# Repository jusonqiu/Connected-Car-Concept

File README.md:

# Connected Car Concept

The Connected Car Project, GateBox, allows you to operate your garage door and front lawn lights from the car's dashboard itself. It does this by having a smartphone interact with a gateway panel (the GateBox panel) that is placed within the garage. The smartphone is mirrored onto the car's dashboard. This is possible using a number of Connected Car features which are likely to grow popular in the future such as: Android Auto, Apple CarPlay, MirrorLink, AppLink, etc. This project was entered into the Microsoft Imagine Cup competition of 2015.

Please watch the introduction video below:

<div style="text-align: center">

</div>

The Github.io page is can be seen [here](http://shafeeqr2.github.io/Connected-Car-Concept/ "GateBox").
## Opensource
Since the Microsoft Imagine Cup competition, this project has been released on Github in hopes that it can be improved upon. The orignal app developed is in the "Windows Application Folder". Some of the files that were submitted to Microsoft judges are in the "Imagine Cup Files" folder. These files have been slightly modified since submission. 

## Where to Start?
First read the Bluetooth manuals. They are from the Bluetooth Special Interest Group and aim to teach how to develop Bluetooth Low Energy applications for a number of different platforms  - Android, iOS and Windows Phone.

For the electronics, there are two different ways to approach this project: The Simplified and Detailed way - One method uses a pre-existing Bluetooth LE chip and other method involves making this chip from scratch based on schematics provided. There is a Parts List and the Instructions version for the detailed and the simplified way. It is recommended that you start with the simplified way even if you plan to use the detailed way.

Read through the parts list for the electronics and the case enclosure in the "Parts List" folder. Then, read through the hardware and software instructions in the "Instructions" folder.

##Contribute

If you feel you can improve on a certain aspect of this project or expand upon it, please considering sharing it to be a part of this project.

If you have any questions or concerns, please contact me at: shafeeqr21@gmail.com.

## What are Connected Cars?

### The following expert is from a 2014 CABA (Continental Automated Building Association) report:

*The connected car market, while still in its infancy, has rapidly evolved from a niche capability available in select models to a perceived must-have in the car industry. A connected car, by definition, is one that maintains a wide area connection (typically cellular-based) and often also a local area network (typically Wi-Fi). Via these connections the car is able to send and receive information relevant to the trip/route and the car’s performance/condition.*

*An increasing number of vehicles are coming to market with the capability to support communications of various sorts. In 2013 more than one billion sensors were sold to the auto industry, more than doubling the 2009 levels[1]. While tethered and integrated solutions have dominated car connectivity to date, embedded connectivity solutions began appearing in 2014 with the number of such vehicles increasing in 2015 and beyond.*

*The connected car market is on the cusp of significant growth. A variety of market factors, from government regulations, to industry partnerships, to consumer demand, are propelling the connected car market forward. Consumers got a glimpse of the future of connected cars in 2014 as select models began rolling off the production line with these capabilities, but 2015 promises so much more in terms of number of connected vehicles and the services being delivered to those vehicles.* 

##

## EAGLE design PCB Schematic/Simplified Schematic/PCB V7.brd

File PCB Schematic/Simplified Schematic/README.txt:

The design can be further simplified if you decide to use your own Arduino UNO in which case you need not include the following materials onto PCB (Refer to "PCB V7 board.PNG"):

* DCJACK
* Diode D1
* Capacitors C1, C2, C3, C4
* ATMEGA328P IC1
* Voltage Regulator 7805T IC2
* Quartz Crystal 16MHZ Q1

It would be nice if someone can take the time to make a PCB without these items and in its place leave a line of male headers which would connect to the Arduino UNO as per the following pinouts:

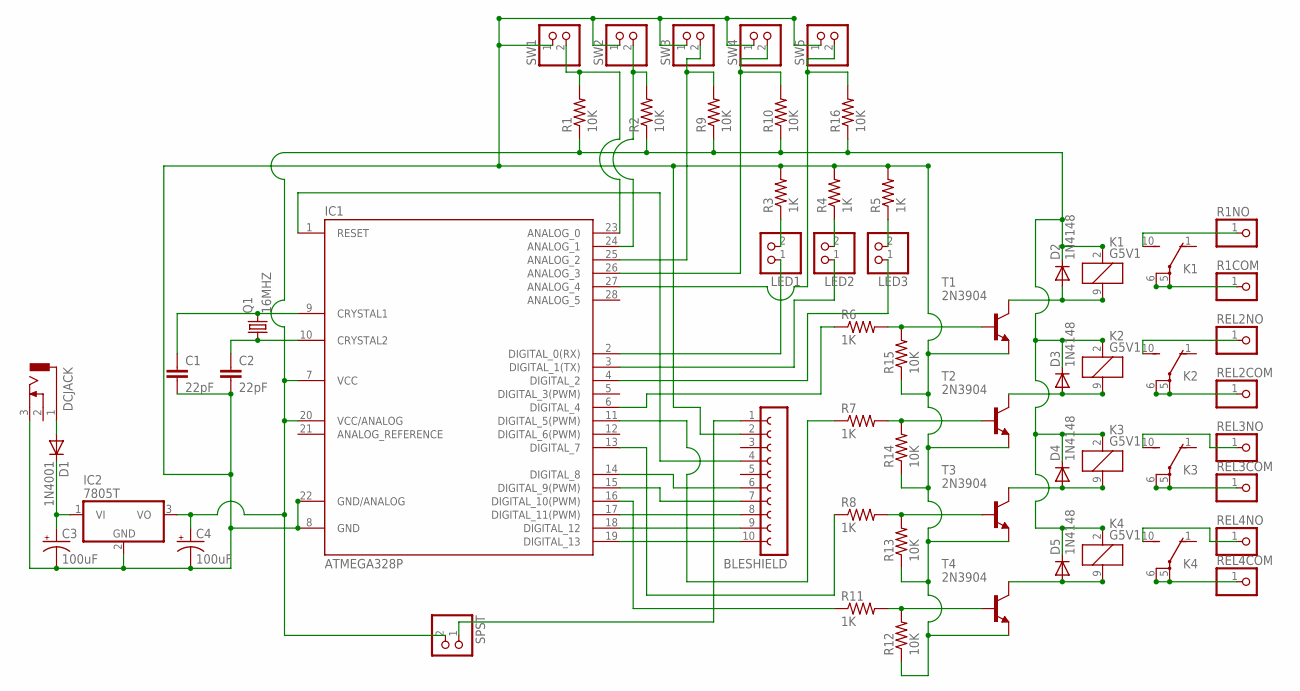
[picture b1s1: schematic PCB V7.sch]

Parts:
BLESHIELD: FE10-1; FE10
C1, C2: 22pF; C025-030X050
C3, C4: 100uF; E2,5-6
D1: 1N4001; DO41-10
D2, D3, D4, D5: 1N4148; DO35-7
DCJACK: DCJ0202
IC1: ATMEGA328P; DIL28-3
IC2: 7805T; TO220H
K1, K2, K3, K4: G5V1
LED1, LED2, LED3: PINHD-1X2; 1X02
Q1: 16MHZ; HC49/S
R1, R2, R9, R10, R12, R13, R14, R15, R16: 10K; 0204/5
R1COM, R1NO: PINHD-1X1; 1X01
R3, R4, R5, R6, R7, R8, R11: 1K; 0204/5
REL2COM, REL2NO, REL3COM, REL3NO, REL4COM, REL4NO: PINHD-1X1; 1X01
SPST: PINHD-1X2; 1X02
SW1, SW2, SW3, SW4, SW5: PINHD-1X2; 1X02
T1, T2, T3, T4: 2N3904; TO92

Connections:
GND: BLESHIELD.2, C1.2, C2.2, C3.-, C4.-, DCJACK.3, IC1.8 (GND), IC1.22 (GND/ANALOG), IC2.2 (GND), R3.2, R4.2, R5.2, R12.1, R13.1, R14.1, R15.1, SW1.1, SW2.1, SW3.1, SW4.1, SW5.1, T1.3 (E), T2.3 (E), T3.3 (E), T4.3 (E)
unnamed: BLESHIELD.10, IC1.19 (DIGITAL_13)
unnamed: R6.2, R15.2, T1.2 (B)
unnamed: IC1.3 (DIGITAL_1(TX)), LED2.1
unnamed: BLESHIELD.6, IC1.14 (DIGITAL_8)
unnamed: C1.1, IC1.9 (CRYSTAL1), Q1.2
unnamed: C2.1, IC1.10 (CRYSTAL2), Q1.1
unnamed: IC1.24 (ANALOG_1), R2.2, SW2.2
unnamed: C3.+, D1.C, IC2.1 (VI)
unnamed: BLESHIELD.4, IC1.1 (RESET)
unnamed: BLESHIELD.7, IC1.15 (DIGITAL_9(PWM))
unnamed: BLESHIELD.8, IC1.17 (DIGITAL_11(PWM))
unnamed: BLESHIELD.9, IC1.18 (DIGITAL_12)
unnamed: D3.A, K2.9 (2), T2.1 (C)
unnamed: R7.2, R14.2, T2.2 (B)
unnamed: IC1.23 (ANALOG_0), R1.2, SW1.2
unnamed: D2.A, K1.9 (2), T1.1 (C)
unnamed: LED1.2, R3.1
unnamed: LED2.2, R4.1
unnamed: LED3.2, R5.1
unnamed: C4.+, D2.C, D3.C, D4.C, D5.C, IC1.7 (VCC), IC1.20 (VCC/ANALOG), IC2.3 (VO), K1.2 (1), K2.2 (1), K3.2 (1), K4.2 (1), R1.1, R2.1, R9.1, R10.1, R16.1, SPST.2
unnamed: IC1.27 (ANALOG_4), R16.2, SW5.2
unnamed: K1.5, K1.6, R1COM.1
unnamed: K1.10 (S), R1NO.1
unnamed: IC1.16 (DIGITAL_10(PWM)), R11.1
unnamed: IC1.25 (ANALOG_2), R9.2, SW3.2
unnamed: IC1.6 (DIGITAL_4), R6.1
unnamed: D1.A, DCJACK.1
unnamed: IC1.26 (ANALOG_3), R10.2, SW4.2
unnamed: IC1.2 (DIGITAL_0(RX)), LED1.1
unnamed: BLESHIELD.1, SPST.1
unnamed: K2.10 (S), REL2NO.1
unnamed: K2.5, K2.6, REL2COM.1
unnamed: K3.5, K3.6, REL3COM.1
unnamed: IC1.13 (DIGITAL_7), R8.1
unnamed: IC1.11 (DIGITAL_5(PWM)), R7.1
unnamed: K3.10 (S), REL3NO.1
unnamed: K4.10 (S), REL4NO.1
unnamed: K4.5, K4.6, REL4COM.1
unnamed: R8.2, R13.2, T3.2 (B)
unnamed: IC1.4 (DIGITAL_2), LED3.1
unnamed: D4.A, K3.9 (2), T3.1 (C)
unnamed: R11.2, R12.2, T4.2 (B)
unnamed: D5.A, K4.9 (2), T4.1 (C)

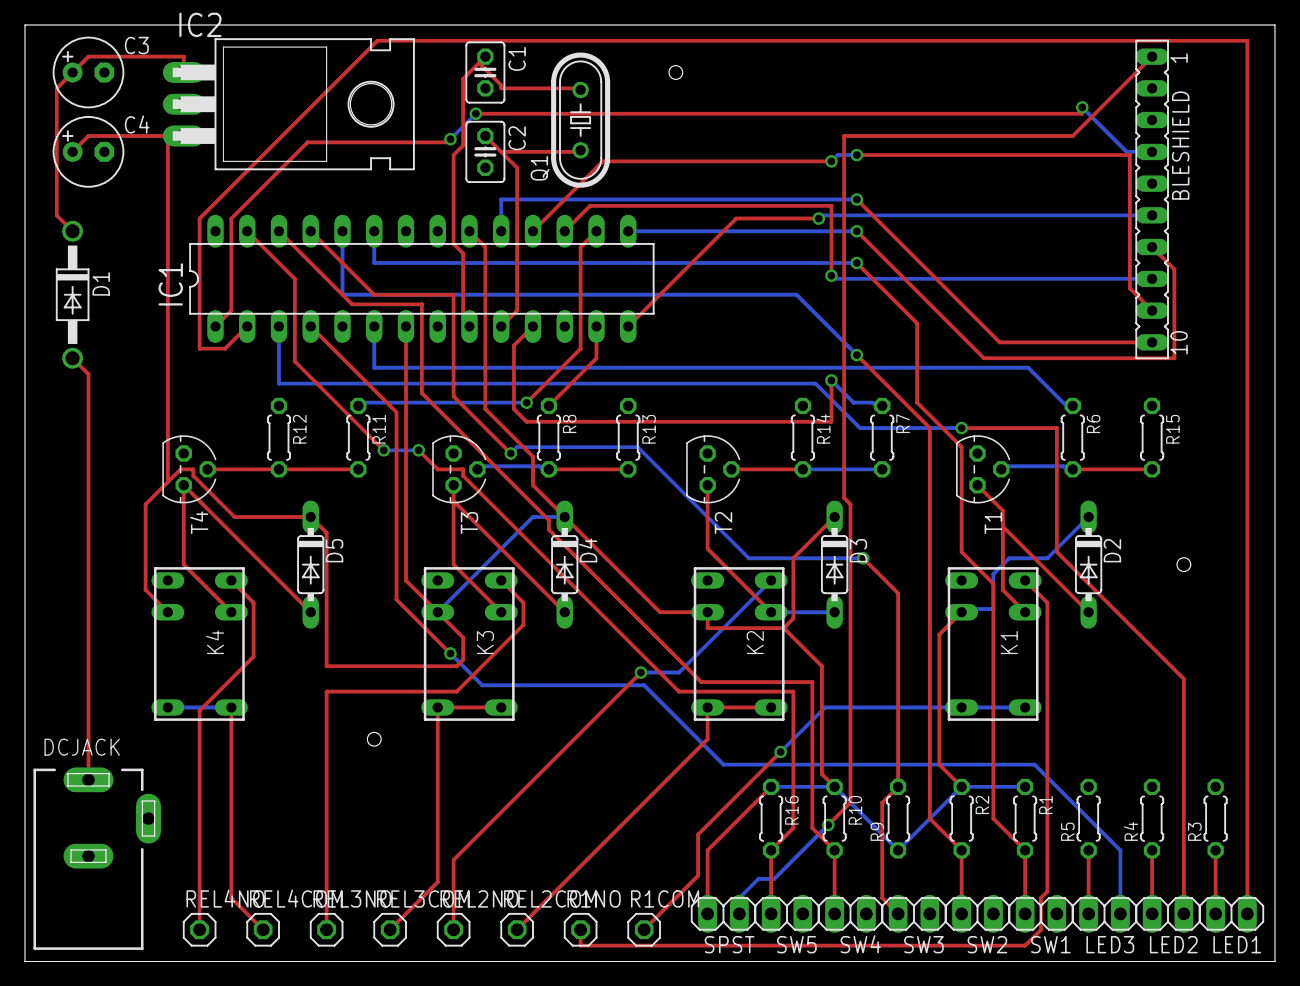
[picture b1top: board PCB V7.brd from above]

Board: 2 copper layers, 100.0 x 74.9 mm, 55 parts (0 on the bottom side), 44 nets.

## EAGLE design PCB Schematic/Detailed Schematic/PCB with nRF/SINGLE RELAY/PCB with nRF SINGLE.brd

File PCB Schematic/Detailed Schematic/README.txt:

The design has been modified since these files have been made.

Would appreciate it if someone could replace the two solid state relays with 4 mechanical relays (as shown in PCB V7 board.PNG in Simplified Schematic folder) and re-route all the wires and push the .brd and .sch files.

Thanks.

Shafeeq.

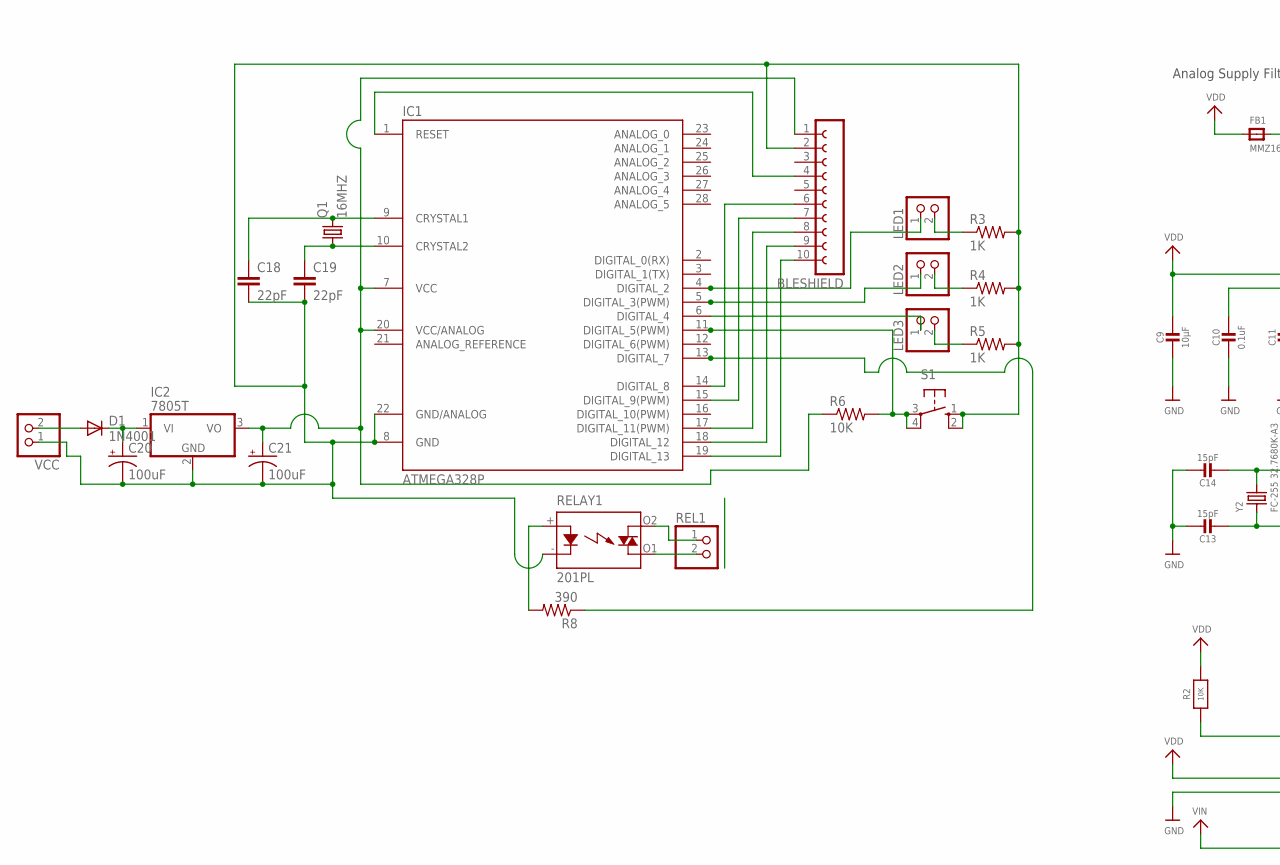
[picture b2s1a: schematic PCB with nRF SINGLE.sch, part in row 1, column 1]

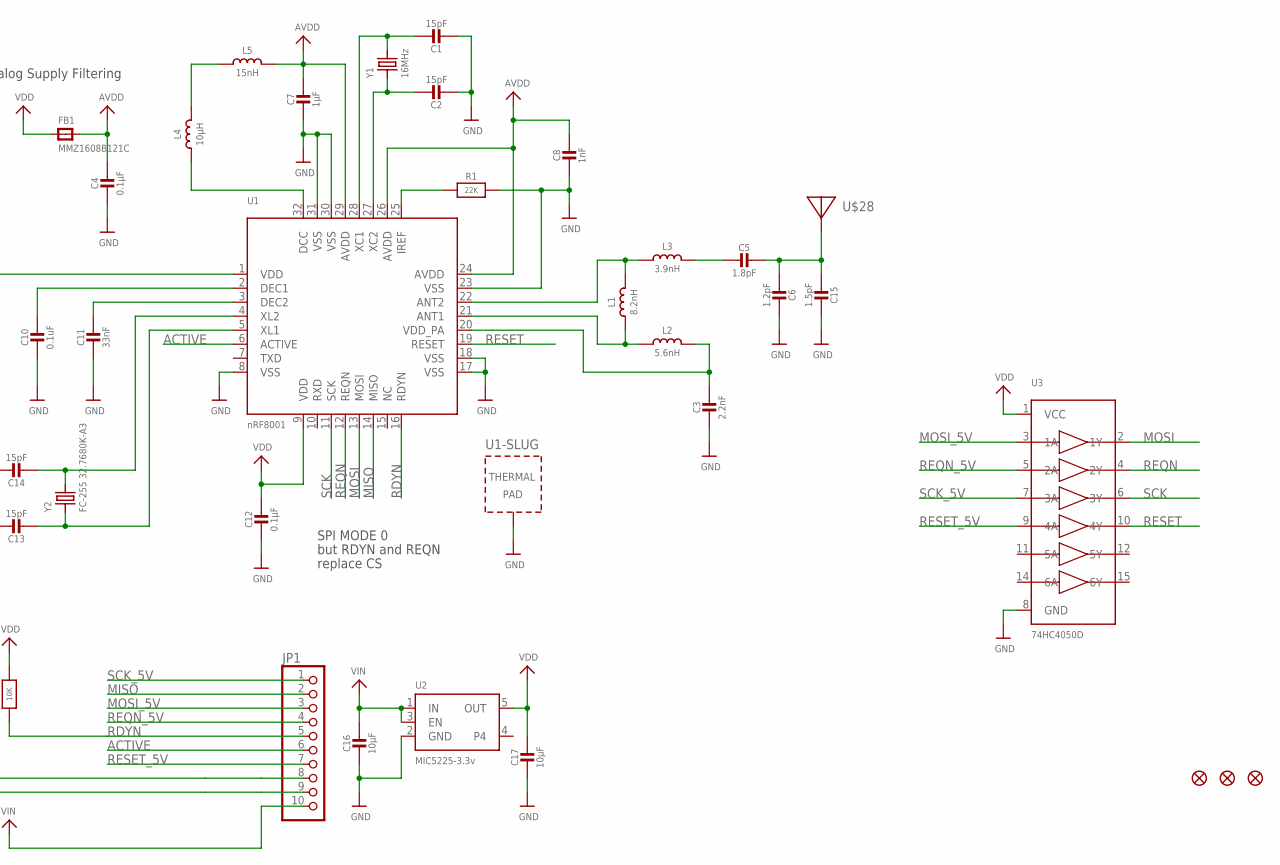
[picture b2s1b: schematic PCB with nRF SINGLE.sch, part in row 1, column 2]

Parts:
BLESHIELD: FE10-1; FE10
C1, C2, C13, C14: 15pF; 0805-NO
C3: 2.2nF; _0402
C4, C12: 0.1µF; 0805-NO
C5: 1.8pF; _0402MP
C6: 1.2pF; _0402MP
C7: 1µF; 0805-NO
C8: 1nF; _0603
C9, C16, C17: 10µF; 0805-NO
C10: 0.1uF; 0805-NO
C11: 33nF; 0805-NO
C15: 1.5pF; _0402MP
C18, C19: 22pF; C025-030X050
C20, C21: 100uF; E2,5-6
D1: 1N4001; DO41-10
FB1: MMZ1608B121C; 0805
FID1, FID2, FID3: FIDUCIAL""; FIDUCIAL_1MM
IC1: ATMEGA328P; DIL28-3
IC2: 7805T; TO220H
JP1: HEADER-1X1070MIL; 1X10_ROUND70
L1: 8.2nH; _0402
L2: 5.6nH; _0402
L3: 3.9nH; _0402
L4: 10µH; _0603
L5: 15nH; _0603
LED1, LED2, LED3: PINHD-1X2; 1X02
Q1: 16MHZ; HC49/S
R1: 22K; _0805MP
R2: 10K; 0805-NO
R3, R4, R5: 1K; 0204/5
R6: 10K; 0204/5
R8: 390; 0204/5
REL1: PINHD-1X2; 1X02
RELAY1: 201PL; AQG
S1: 10-XX; B3F-10XX
U1: nRF8001; QFN32_5MM
U2: MIC5225-3.3v; SOT23-5
U3: 74HC4050D; TSSOP16
U$28: ANTENNA_PCBNRF8001_1.6MM; ANT_PCB_2.4GHZ_NRF8001_1.6MM_1OZ
VCC: PINHD-1X2; 1X02
Y1: 16MHz; CRYSTAL_2.5X2
Y2: FC-255 32.7680K-A3; CRYSTAL_4.9X1.8

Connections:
ACTIVE: JP1.6, U1.6 (ACTIVE)
AVDD: C4.1, C7.1, C8.1, FB1.2, L5.2, U1.24 (AVDD), U1.26 (AVDD), U1.29 (AVDD)
GND: C1.2, C2.2, C3.2, C4.2, C6.1, C7.2, C8.2, C9.2, C10.2, C11.2, C12.2, C13.1, C14.1, C15.1, C16.2, C17.2, JP1.9, R1.2, U1.8 (VSS), U1.17 (VSS), U1.18 (VSS), U1.23 (VSS), U1.30 (VSS), U1.31 (VSS), U1.33 (TP), U2.2 (GND), U3.8 (GND)
MISO: JP1.2, U1.14 (MISO)
MOSI: U1.13 (MOSI), U3.2 (1Y)
MOSI_5V: JP1.3, U3.3 (1A)
unnamed: BLESHIELD.10, IC1.19 (DIGITAL_13)
unnamed: L1.2, L3.1, U1.22 (ANT2)
unnamed: L1.1, L2.1, U1.21 (ANT1)
unnamed: C3.1, L2.2, U1.20 (VDD_PA)
unnamed: L4.2, L5.1
unnamed: C5.2, L3.2
unnamed: C11.1, U1.3 (DEC2)
unnamed: C10.1, U1.2 (DEC1)
unnamed: C1.1, U1.28 (XC1), Y1.3 (2)
unnamed: C2.1, U1.27 (XC2), Y1.1
unnamed: L4.1, U1.32 (DCC)
unnamed: R1.1, U1.25 (IREF)
unnamed: C5.1, C6.2, C15.2, U$28.FEED
unnamed: C18.1, IC1.9 (CRYSTAL1), Q1.2
unnamed: C19.1, IC1.10 (CRYSTAL2), Q1.1
unnamed: BLESHIELD.6, IC1.14 (DIGITAL_8)
unnamed: BLESHIELD.7, IC1.15 (DIGITAL_9(PWM))
unnamed: BLESHIELD.8, IC1.17 (DIGITAL_11(PWM))
unnamed: BLESHIELD.9, IC1.18 (DIGITAL_12)
unnamed: BLESHIELD.1, C21.+, IC1.7 (VCC), IC1.20 (VCC/ANALOG), IC2.3 (VO), R6.1
unnamed: BLESHIELD.4, IC1.1 (RESET)
unnamed: C14.2, U1.4 (XL2), Y2.2
unnamed: C13.2, U1.5 (XL1), Y2.1
unnamed: IC1.4 (DIGITAL_2), LED1.1
unnamed: IC1.5 (DIGITAL_3(PWM)), LED2.1
unnamed: LED1.2, R3.1
unnamed: LED2.2, R4.1
unnamed: LED3.2, R5.1
unnamed: IC1.11 (DIGITAL_5(PWM)), R6.2, S1.3, S1.4 (P1)
unnamed: REL1.2, RELAY1.O1 (DS2)
unnamed: IC1.13 (DIGITAL_7), R8.1
unnamed: C20.+, D1.C, IC2.1 (VI)
unnamed: BLESHIELD.2, C18.2, C19.2, C20.-, C21.-, IC1.8 (GND), IC1.22 (GND/ANALOG), IC2.2 (GND), R3.2, R4.2, R5.2, RELAY1.- (K), S1.1 (S), S1.2 (S1), VCC.1
unnamed: D1.A, VCC.2
unnamed: IC1.6 (DIGITAL_4), LED3.1
unnamed: R8.2, RELAY1.+ (A)
RDYN: JP1.5, R2.1, U1.16 (RDYN)
REL1: REL1.1, RELAY1.O2 (DS1)
REQN: U1.12 (REQN), U3.4 (2Y)
REQN_5V: JP1.4, U3.5 (2A)
RESET: U1.19 (RESET), U3.10 (4Y)
RESET_5V: JP1.7, U3.9 (4A)
SCK: U1.11 (SCK), U3.6 (3Y)
SCK_5V: JP1.1, U3.7 (3A)
VDD: C9.1, C12.1, C17.1, FB1.1, JP1.8, R2.2, U1.1 (VDD), U1.9 (VDD), U2.5 (OUT), U3.1 (VCC)
VIN: C16.1, JP1.10, U2.1 (IN), U2.3 (EN)

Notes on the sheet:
Analog Supply Filtering
SPI MODE 0
but RDYN and REQN
replace CS

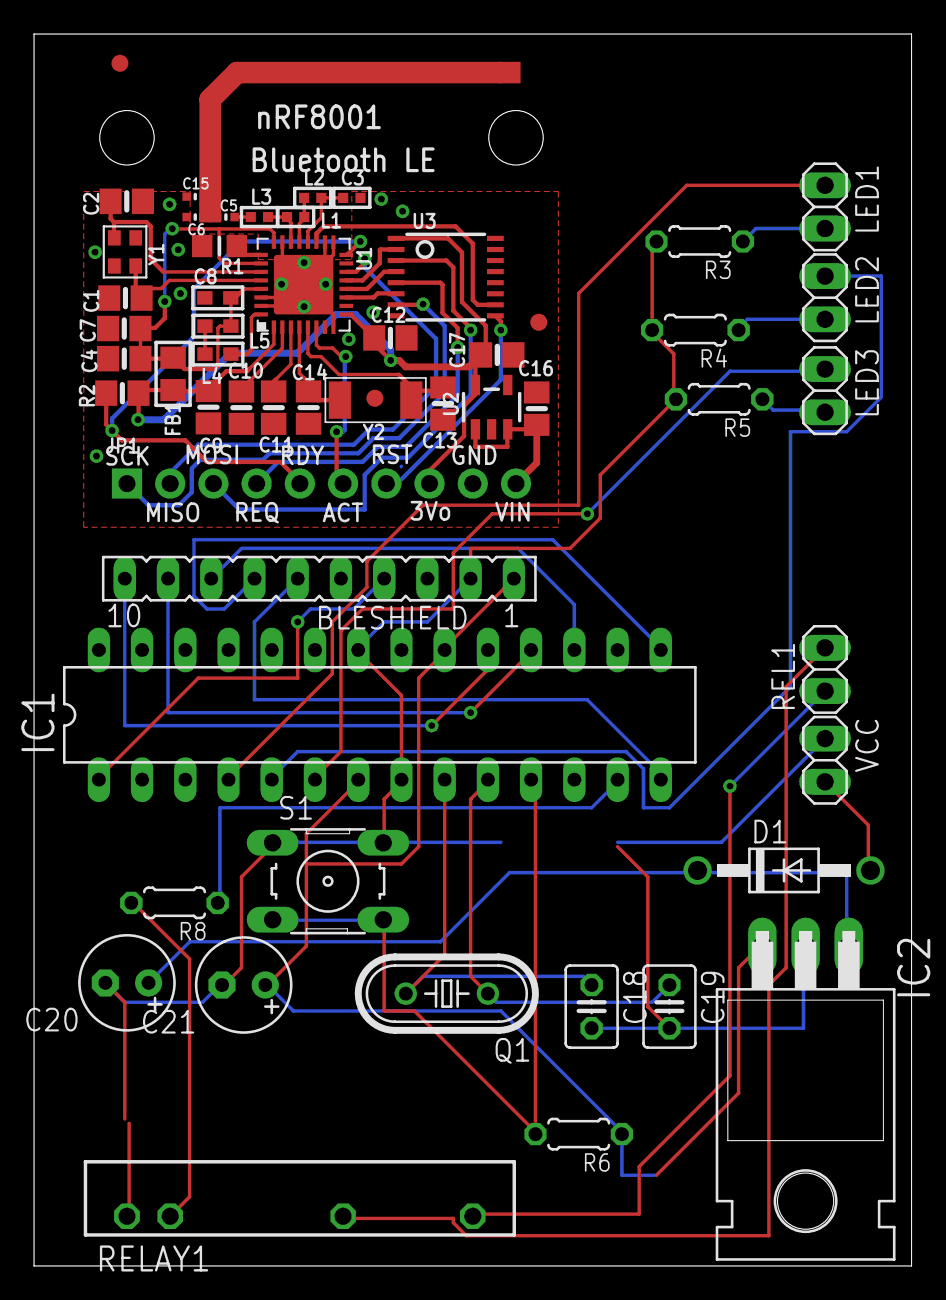
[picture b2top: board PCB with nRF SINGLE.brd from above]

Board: 2 copper layers, 51.6 x 72.4 mm, 57 parts (1 on the bottom side), 52 nets.

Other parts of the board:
U$22: ADAFRUIT_TEXT_20MM

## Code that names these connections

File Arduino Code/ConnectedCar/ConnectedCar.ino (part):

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
  //Tell the ACI library, the MCU to nRF8001 pin connections
  aci_state.aci_pins.board_name = BOARD_DEFAULT; //See board.h for details
  aci_state.aci_pins.reqn_pin   = 9;
  aci_state.aci_pins.rdyn_pin   = 8;
  aci_state.aci_pins.mosi_pin   = MOSI;
  aci_state.aci_pins.miso_pin   = MISO;
  aci_state.aci_pins.sck_pin    = SCK;
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                                                             //SPI_CLOCK_DIV16 = 1MHz SPI speed

  //aci_state.aci_pins.reset_pin              = 4; //4 for Nordic board, UNUSED for REDBEARLABS
  aci_state.aci_pins.active_pin             = UNUSED;
  aci_state.aci_pins.optional_chip_sel_pin  = UNUSED;

  aci_state.aci_pins.interface_is_interrupt = false;
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
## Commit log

2016-03-12 Create gh-pages branch via GitHub
2016-03-12 The Connected Car Project
2016-03-12 MIT License
2016-03-12 BlueBox folder
2016-03-12 Windows Phone Application
2016-03-12 Update on Software Needed

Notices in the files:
Arduino Code/ConnectedCar/ConnectedCar.ino:
Copyright (c) 2014, Nordic Semiconductor ASA
Hexadecimal sring to decimal string converter by Ben Rugg (www.benrugg.com) made available under the MIT License.
parts and their libraries:
microbuilder: This work is placed in the public domain, and may be freely used for commercial and non-commercial work with the following conditions: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
